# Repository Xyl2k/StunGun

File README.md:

Stun Gun
=======

Eagle typon based on the 555 stun gun circuit found on http://www.555-timer-circuits.com/stun-gun.html
Typon made for the issue 4 of HackerStrip (hackerstrip.com)
Please note that i haven't tested to produce my pcb and even the circuit.

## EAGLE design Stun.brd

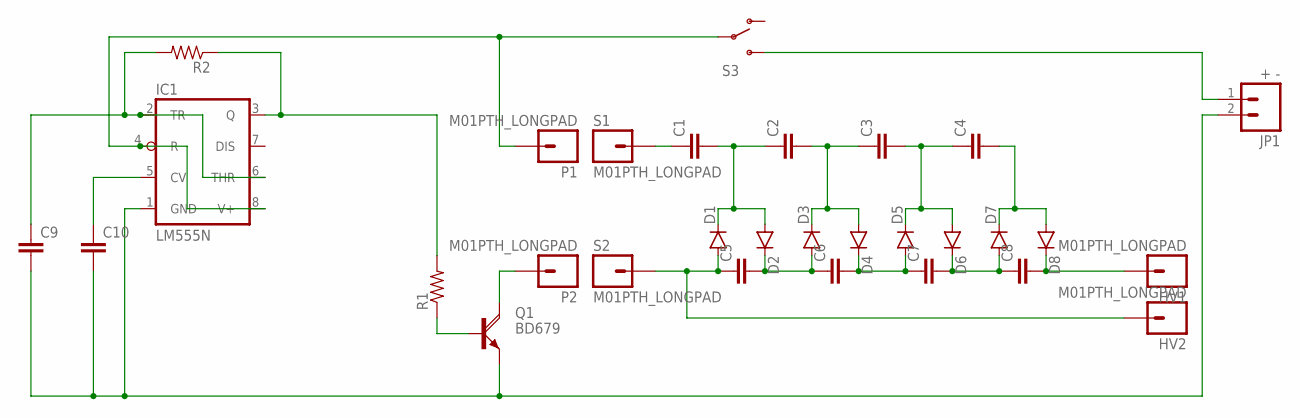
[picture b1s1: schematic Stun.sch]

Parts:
C1, C2, C3, C4, C5, C6, C7, C8: CAPPTH1; CAP-PTH-5MM
C9, C10: 0.1UF-50V-20%(PTH)KIT-EZ; CAP-PTH-SMALL-KIT
D1, D2, D3, D4, D5, D6, D7, D8: DIODE; DIODE-1N4001-KIT
HV1, HV2: M01PTH_LONGPAD; 1X01_LONGPAD
IC1: LM555N; DIL08-ROUND
JP1: + -; 1X02
P1, P2: M01PTH_LONGPAD; 1X01_LONGPAD
Q1: BD679; TO126AV
R1, R2: RESISTORPTH-1/4W; AXIAL-0.4
S1, S2: M01PTH_LONGPAD; 1X01_LONGPAD
S3: SWITCH-SPDTPTH; SWITCH-SPDT

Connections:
12V: JP1.1, S3.3 (S)
GND: C9.2, C10.2, IC1.1 (GND), JP1.2, Q1.E
unnamed: C5.1, D1.A, HV2.1, S2.1
unnamed: C5.2, C6.1, D2.C, D3.A
unnamed: Q1.B, R1.P$1 (1)
unnamed: C6.2, C7.1, D4.C, D5.A
unnamed: IC1.3 (Q), R1.P$2 (2), R2.P$1 (1)
unnamed: C9.1, IC1.2 (TR), IC1.6 (THR), R2.P$2 (2)
unnamed: C7.2, C8.1, D6.C, D7.A
unnamed: C4.2, D7.C, D8.A
unnamed: C8.2, D8.C, HV1.1
unnamed: C1.2, C2.1, D1.C, D2.A
unnamed: C2.2, C3.1, D3.C, D4.A
unnamed: C3.2, C4.1, D5.C, D6.A
unnamed: C1.1, S1.1
unnamed: P2.1, Q1.C
unnamed: IC1.4 (R), IC1.8 (V+), P1.1, S3.2
unnamed: C10.1, IC1.5 (CV)

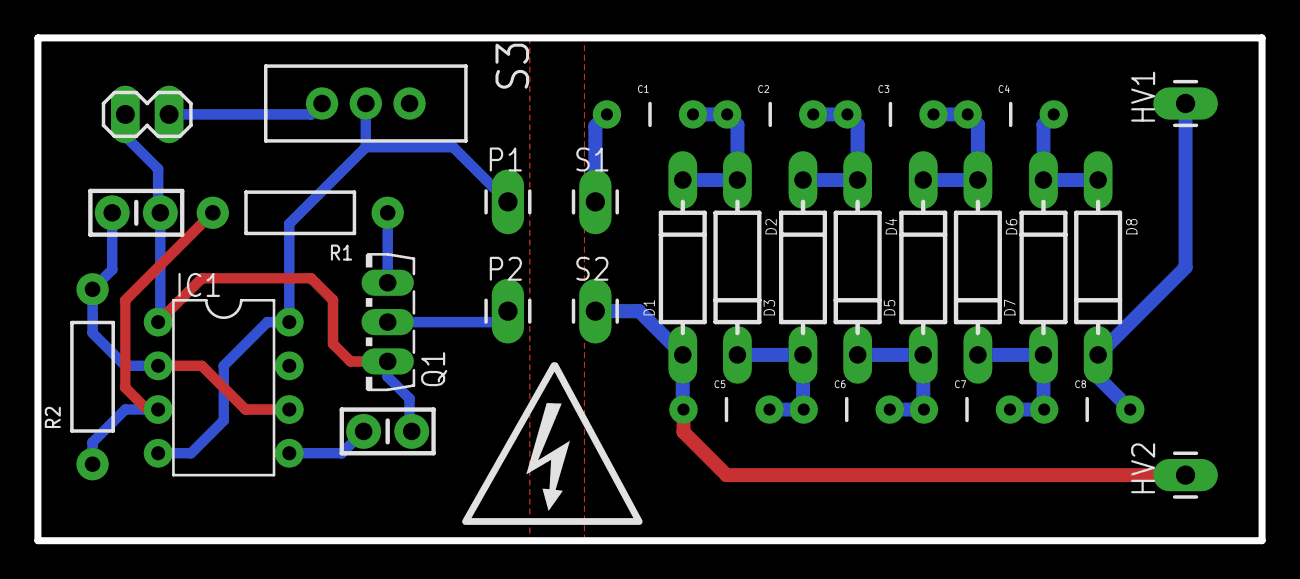
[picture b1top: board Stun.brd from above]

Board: 2 copper layers, 71.1 x 29.2 mm, 30 parts (0 on the bottom side), 18 nets.

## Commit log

2014-12-04 :octocat: Added .gitattributes & .gitignore files
2014-12-04 1.0
    1.0

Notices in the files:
parts and their libraries:
SparkFun-DiscreteSemi: Licensing: Creative Commons ShareAlike 4.0 International - https://creativecommons.org/licenses/by-sa/4.0
